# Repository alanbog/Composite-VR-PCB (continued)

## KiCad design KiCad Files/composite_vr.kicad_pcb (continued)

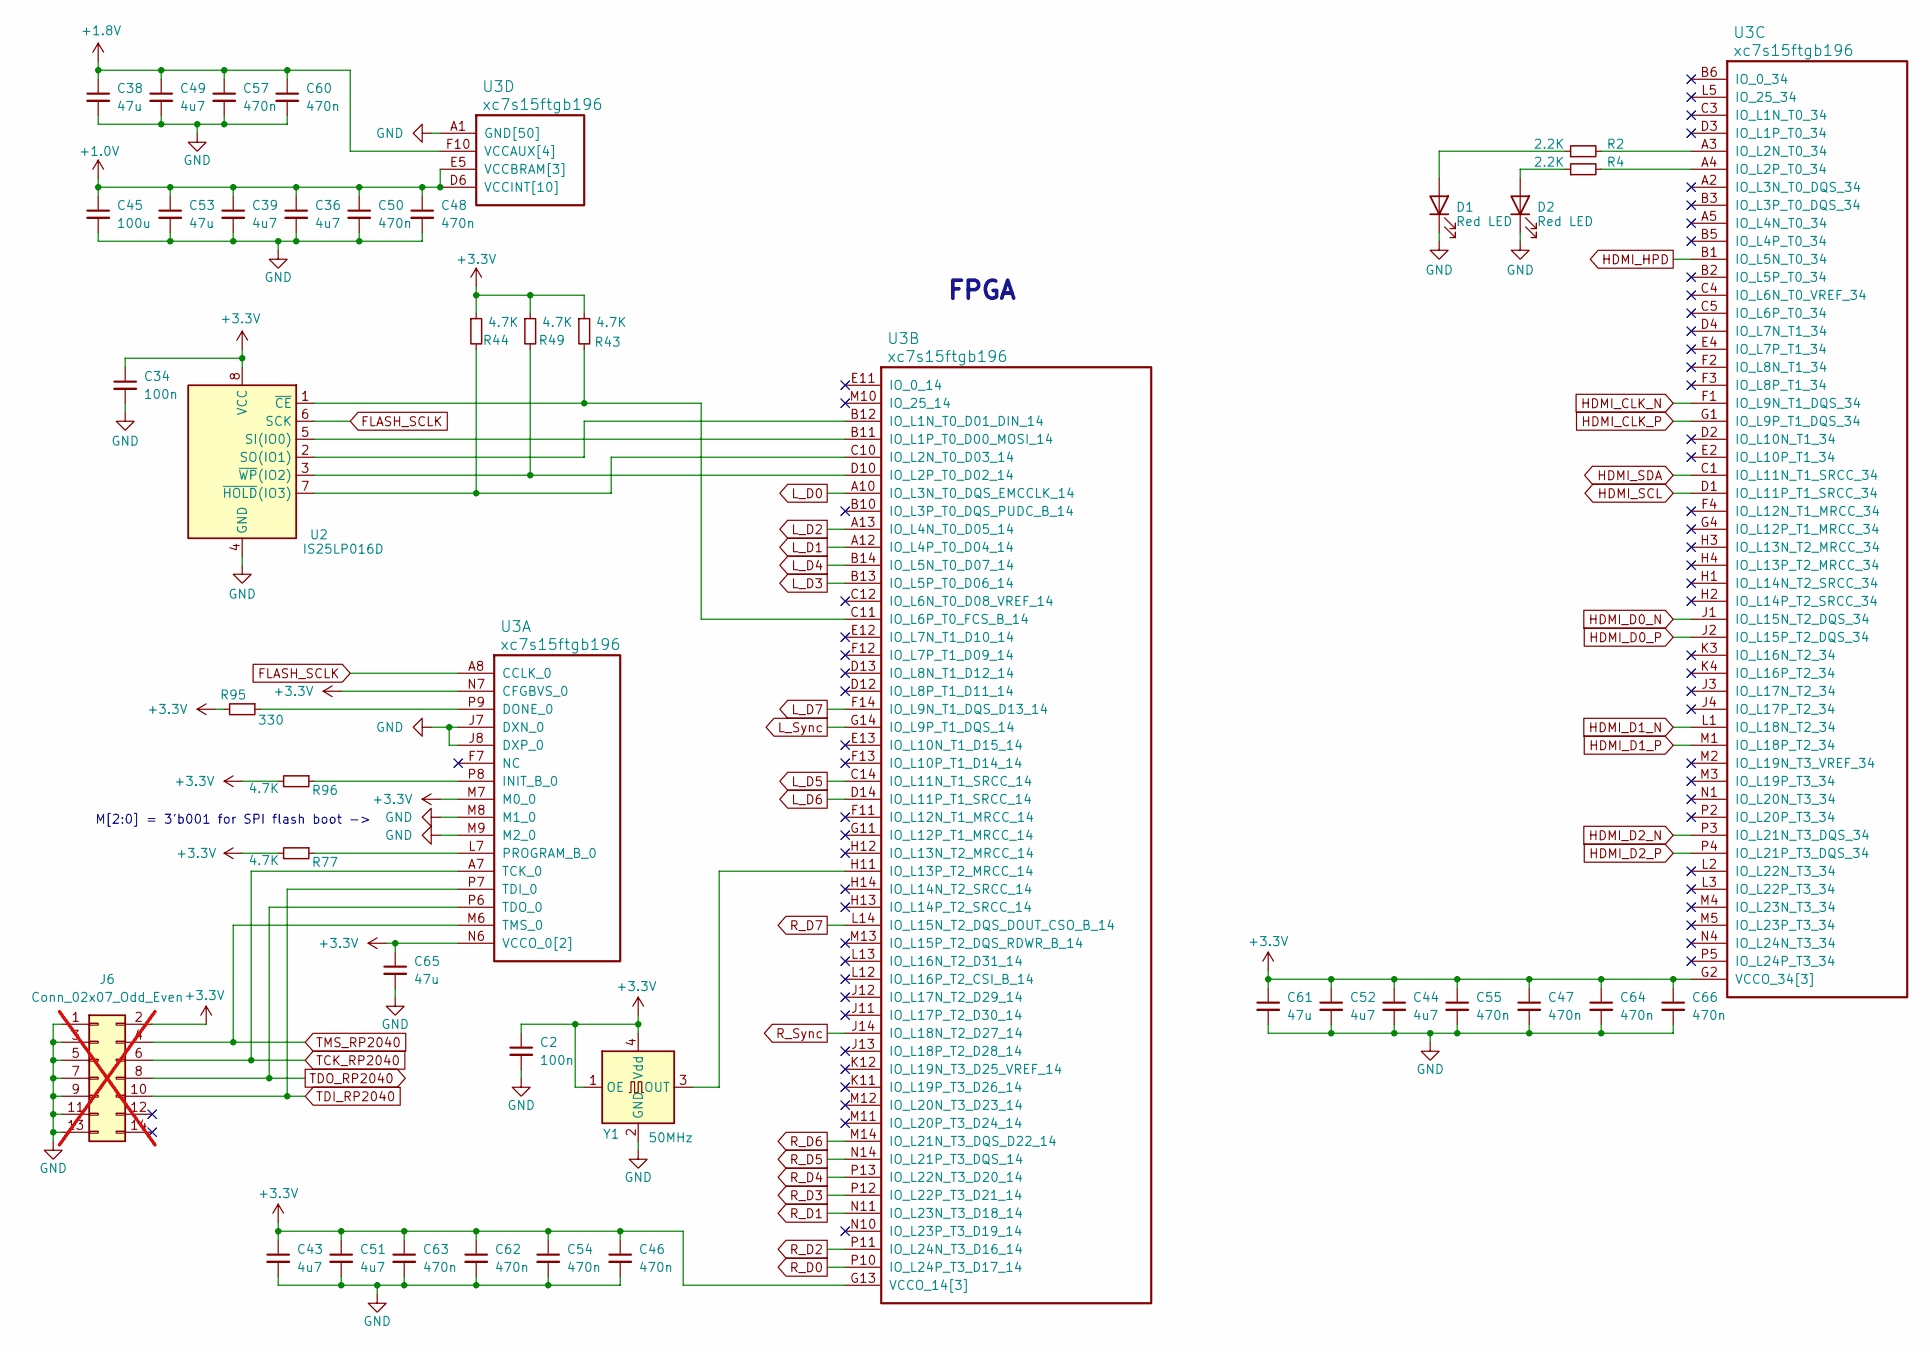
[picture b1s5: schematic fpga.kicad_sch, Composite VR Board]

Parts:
C2, C34: 100n; C_0402; Rating 16V; Tolerance 10%; Mfg PN CL05B104KO5NNNC; JLCPCB C1525
C36, C39, C43, C44, C49, C51, C52: 4u7; C_0402; Rating 10V; Tolerance 20%; Mfg PN CL05A475MP5NRNC; JLCPCB C23733
C38, C53, C61, C65: 47u; C_0805; Rating 6.3V; Tolerance 20%; Mfg PN CL21A476MQYNNNE; JLCPCB C16780
C45: 100u; C_1206; Rating 6.3V; Tolerance 20%; Mfg PN CL31A107MQHNNNE; JLCPCB C15008
C46, C47, C48, C50, C54, C55, C57, C60, C62, C63, C64, C66: 470n; C_0402; Rating 10V; Tolerance 10%; Mfg PN CL05A474KP5NNNC; JLCPCB C47339
D1, D2: Red LED; LED_0603_1608Metric; Mfg PN KT-0603R; JLCPCB C2286
J6: Conn_02x07_Odd_Even; PinHeader_2x07_P2.00mm_Vertical_SMD; not fitted
R2, R4: 2.2K; R_0402; Rating 62.5mW; Tolerance 1%; Mfg PN 0402WGF2201TCE; JLCPCB C25879
R43, R44, R49, R77, R96: 4.7K; R_0402; Rating 62.5mW; Tolerance 1%; Mfg PN 0402WGF4701TCE; JLCPCB C25900
R95: 330; R_0402; Rating 62.5mW; Tolerance 1%; Mfg PN 0402WGF3300TCE; JLCPCB C25104
U2: IS25LP016D; SO-8_3.9x4.9mm_P1.27mm; Mfg PN IS25LP016D-JNLE-TR; JLCPCB C2653501
U3: xc7s15ftgb196; Xilinx_FTGB196; Mfg PN XC7S15-2FTGB196I; JLCPCB C1521865
Y1: 50MHz; Oscillator_SMD_SiT_PQFN-4Pin_3.2x2.5mm; Mfg PN SiT8008BI-22-33E-50.000000; JLCPCB C26267

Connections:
+1.0V: C36.1, C39.1, C45.1, C48.1, C50.1, C53.1, U3.D6 (VCCINT[10]), U3.D8 (VCCINT[10]), U3.E5 (VCCBRAM[3]), U3.E7 (VCCINT[10]), U3.E9 (VCCINT[10]), U3.F6 (VCCINT[10]), U3.G5 (VCCBRAM[3]), U3.G9 (VCCINT[10]), U3.H6 (VCCINT[10]), U3.J5 (VCCBRAM[3]), U3.J9 (VCCINT[10]), U3.K6 (VCCINT[10]), U3.K8 (VCCINT[10]); also elsewhere on the board
+1.8V: C38.1, C49.1, C57.1, C60.1, U3.F10 (VCCAUX[4]), U3.H10 (VCCAUX[4]), U3.K10 (VCCAUX[4]), U3.L9 (VCCAUX[4]); also elsewhere on the board
+3.3V: C2.1, C34.1, C43.1, C44.1, C46.1, C47.1, C51.1, C52.1, C54.1, C55.1, C61.1, C62.1, C63.1, C64.1, C65.1, C66.1, J6.2, R43.1, R44.1, R49.1, R77.2, R95.2, R96.2, U2.8 (VCC), U3.G2 (VCCO_34[3]), U3.G13 (VCCO_14[3]), U3.K2 (VCCO_34[3]), U3.K13 (VCCO_14[3]), U3.M7 (M0_0), U3.N2 (VCCO_34[3]), U3.N6 (VCCO_0[2]), U3.N7 (CFGBVS_0), U3.N8 (VCCO_0[2]), U3.N13 (VCCO_14[3]), Y1.1 (OE), Y1.4 (Vdd); also elsewhere on the board
FLASH_SCLK: U2.6 (SCK), U3.A8 (CCLK_0)
GND: C2.2, C34.2, C36.2, C38.2, C39.2, C43.2, C44.2, C45.2, C46.2, C47.2, C48.2, C49.2, C50.2, C51.2, C52.2, C53.2, C54.2, C55.2, C57.2, C60.2, C61.2, C62.2, C63.2, C64.2, C65.2, C66.2, D1.1 (K), D2.1 (K), J6.1, J6.3, J6.5, J6.7, J6.9, J6.11, J6.13, U2.4 (GND), U3.A1 (GND[50]), U3.A6 (GND[50]), U3.A9 (GND[50]), U3.A11 (GND[50]), U3.A14 (GND[50]), U3.B4 (GND[50]), U3.B7 (GND[50]), U3.B9 (GND[50]), U3.C2 (GND[50]), U3.C6 (GND[50]), U3.C7 (GND[50]), U3.C8 (GND[50]), U3.C9 (GND[50]), U3.C13 (GND[50]), U3.D5 (GND[50]), U3.D7 (GND[50]), U3.D9 (GND[50]), U3.D11 (GND[50]), U3.E1 (GND[50]), U3.E3 (GND[50]), U3.E6 (GND[50]), U3.E8 (GND[50]), U3.E10 (GND[50]), U3.E14 (GND[50]), U3.F5 (GND[50]), U3.F9 (GND[50]), U3.G3 (GND[50]), U3.G6 (GND[50]), U3.G10 (GND[50]), U3.G12 (GND[50]), U3.H5 (GND[50]), U3.H9 (GND[50]), U3.J6 (GND[50]), U3.J7 (DXN_0), U3.J8 (DXP_0), U3.J10 (GND[50]), U3.K1 (GND[50]), U3.K5 (GND[50]), U3.K7 (GND[50]), U3.K9 (GND[50]), U3.K14 (GND[50]), U3.L4 (GND[50]), U3.L6 (GND[50]), U3.L8 (GND[50]), U3.L10 (GND[50]), U3.L11 (GND[50]), U3.M8 (M1_0), U3.M9 (M2_0), U3.N3 (GND[50]), U3.N5 (GND[50]), U3.N9 (GND[50]), U3.N12 (GND[50]), U3.P1 (GND[50]), U3.P14 (GND[50]), Y1.2 (GND); also elsewhere on the board
HDMI_CLK_N: U3.F1 (IO_L9N_T1_DQS_34); also elsewhere on the board
HDMI_CLK_P: U3.G1 (IO_L9P_T1_DQS_34); also elsewhere on the board
HDMI_D0_N: U3.J1 (IO_L15N_T2_DQS_34); also elsewhere on the board
HDMI_D0_P: U3.J2 (IO_L15P_T2_DQS_34); also elsewhere on the board
HDMI_D1_N: U3.L1 (IO_L18N_T2_34); also elsewhere on the board
HDMI_D1_P: U3.M1 (IO_L18P_T2_34); also elsewhere on the board
HDMI_D2_N: U3.P3 (IO_L21N_T3_DQS_34); also elsewhere on the board
HDMI_D2_P: U3.P4 (IO_L21P_T3_DQS_34); also elsewhere on the board
HDMI_HPD: U3.B1 (IO_L5N_T0_34); also elsewhere on the board
HDMI_SCL: U3.D1 (IO_L11P_T1_SRCC_34); also elsewhere on the board
HDMI_SDA: U3.C1 (IO_L11N_T1_SRCC_34); also elsewhere on the board
L_D0: U3.A10 (IO_L3N_T0_DQS_EMCCLK_14); also elsewhere on the board
L_D1: U3.A12 (IO_L4P_T0_D04_14); also elsewhere on the board
L_D2: U3.A13 (IO_L4N_T0_D05_14); also elsewhere on the board
L_D3: U3.B13 (IO_L5P_T0_D06_14); also elsewhere on the board
L_D4: U3.B14 (IO_L5N_T0_D07_14); also elsewhere on the board
L_D5: U3.C14 (IO_L11N_T1_SRCC_14); also elsewhere on the board
L_D6: U3.D14 (IO_L11P_T1_SRCC_14); also elsewhere on the board
L_D7: U3.F14 (IO_L9N_T1_DQS_D13_14); also elsewhere on the board
L_Sync: U3.G14 (IO_L9P_T1_DQS_14); also elsewhere on the board
unnamed: D1.2 (A), R2.1
unnamed: D2.2 (A), R4.1
unnamed: U2.5 (SI(IO0)), U3.B11 (IO_L1P_T0_D00_MOSI_14)
unnamed: U2.2 (SO(IO1)), U3.B12 (IO_L1N_T0_D01_DIN_14)
unnamed: R43.2, U2.1 (~CE), U3.C11 (IO_L6P_T0_FCS_B_14)
unnamed: R44.2, U2.7 (~HOLD(IO3)), U3.C10 (IO_L2N_T0_D03_14)
unnamed: R49.2, U2.3 (~WP(IO2)), U3.D10 (IO_L2P_T0_D02_14)
unnamed: R95.1, U3.P9 (DONE_0)
unnamed: R96.1, U3.P8 (INIT_B_0)
unnamed: R77.1, U3.L7 (PROGRAM_B_0)
unnamed: U3.H11 (IO_L13P_T2_MRCC_14), Y1.3 (OUT)
unnamed: R2.2, U3.A3 (IO_L2N_T0_34)
unnamed: R4.2, U3.A4 (IO_L2P_T0_34)
R_D0: U3.P10 (IO_L24P_T3_D17_14); also elsewhere on the board
R_D1: U3.N11 (IO_L23N_T3_D18_14); also elsewhere on the board
R_D2: U3.P11 (IO_L24N_T3_D16_14); also elsewhere on the board
R_D3: U3.P12 (IO_L22P_T3_D21_14); also elsewhere on the board
R_D4: U3.P13 (IO_L22N_T3_D20_14); also elsewhere on the board
R_D5: U3.N14 (IO_L21P_T3_DQS_14); also elsewhere on the board
R_D6: U3.M14 (IO_L21N_T3_DQS_D22_14); also elsewhere on the board
R_D7: U3.L14 (IO_L15N_T2_DQS_DOUT_CSO_B_14); also elsewhere on the board
R_Sync: U3.J14 (IO_L18N_T2_D27_14); also elsewhere on the board
TCK_RP2040: J6.6, U3.A7 (TCK_0); also elsewhere on the board
TDI_RP2040: J6.10, U3.P7 (TDI_0); also elsewhere on the board
TDO_RP2040: J6.8, U3.P6 (TDO_0); also elsewhere on the board
TMS_RP2040: J6.4, U3.M6 (TMS_0); also elsewhere on the board

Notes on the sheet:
FPGA
M[2:0] = 3'b001 for SPI flash boot ->

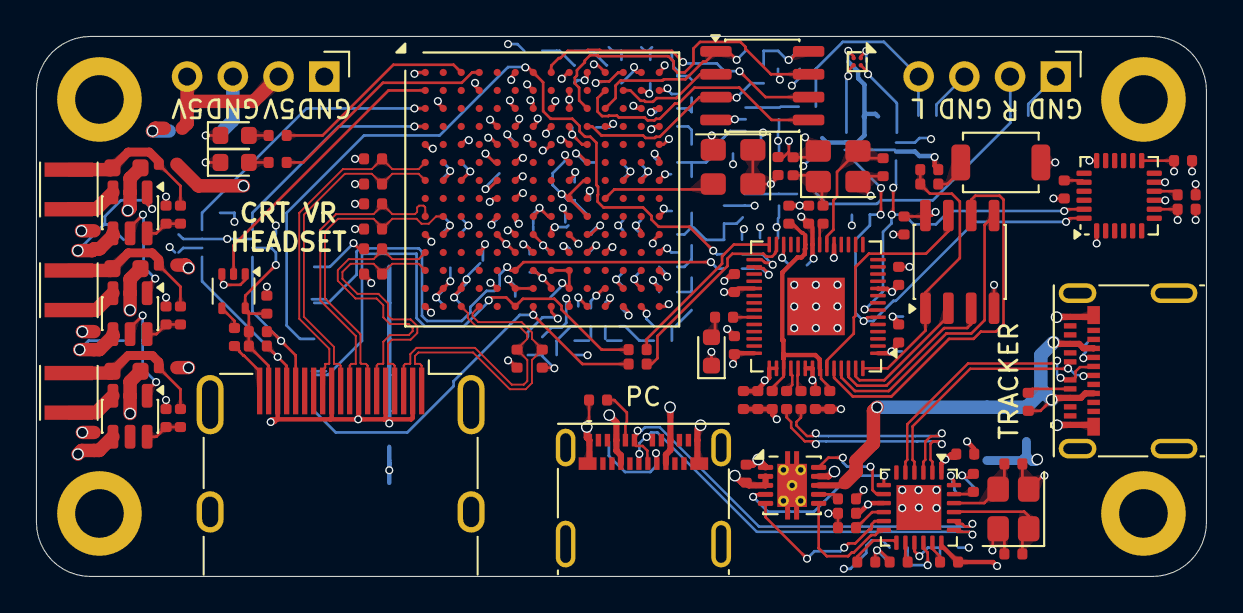
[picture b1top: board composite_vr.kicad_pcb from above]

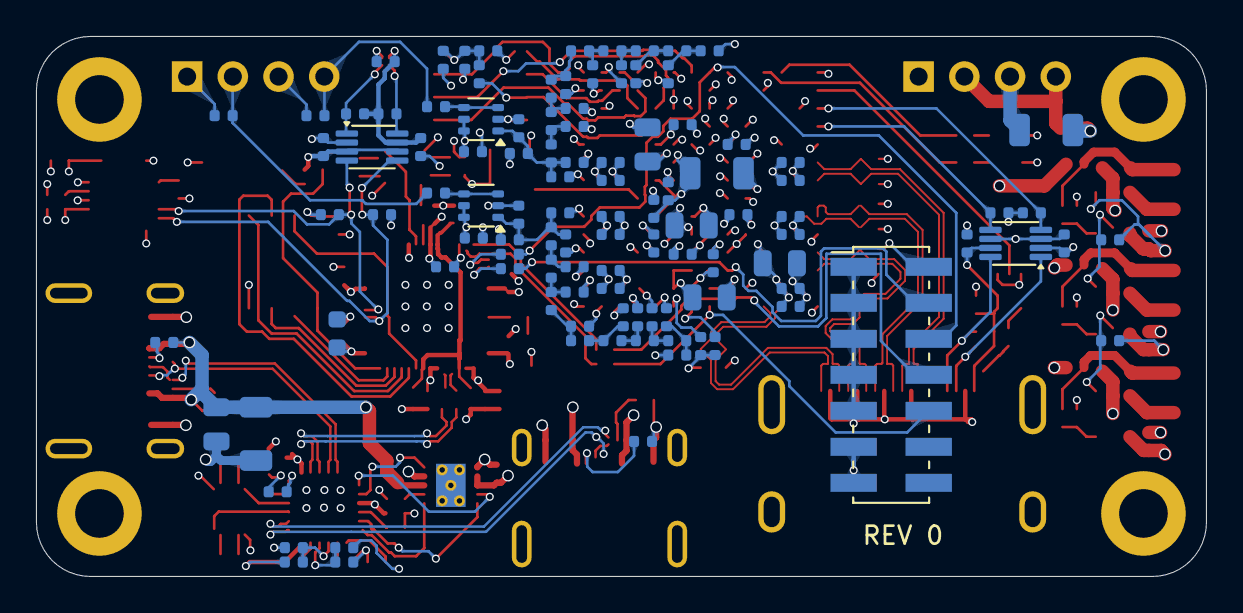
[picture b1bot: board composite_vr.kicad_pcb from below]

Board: 4 copper layers, 65.0 x 30.0 mm, 208 parts (107 on the bottom side), 142 nets.

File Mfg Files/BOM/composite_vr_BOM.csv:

"Reference","Qty","Value","Tolerance","Rating","DNP","Footprint","Mfg","Mfg PN","JLCPCB"
"C1,C2,C7,C8,C9,C10,C11,C14,C15,C16,C17,C19,C21,C24,C25,C27,C29,C30,C34,C42,C56,C58,C59,C70","24","100n","10%","16V","","PCM_JLCPCB:C_0402","Samsung Electro-Mechanics","CL05B104KO5NNNC","C1525"
"C3,C5,C28,C33","4","15p","5%","50V","","PCM_JLCPCB:C_0402","FH (Guangdong Fenghua Advanced Tech)"," 0402CG150J500NT","C1548"
"C4,C13,C20,C67","4","10u","10%","10V","","PCM_JLCPCB:C_0603","Samsung Electro-Mechanics","CL10A106KP8NNNC","C19702"
"C6","1","2.2n","10%","50V","","PCM_JLCPCB:C_0402","FH (Guangdong Fenghua Advanced Tech)","0402B222K500NT","C1531"
"C12,C18,C26,C36,C39,C43,C44,C49,C51,C52","10","4u7","20%","10V","","PCM_JLCPCB:C_0402","Samsung Electro-Mechanics","CL05A475MP5NRNC","C23733"
"C22,C23,C31,C32","4","1u","10%","25V","","PCM_JLCPCB:C_0402","Samsung Electro-Mechanics","CL05A105KA5NQNC","C52923"
"C35,C40,C41","3","100n","10%","16V","DNP","PCM_JLCPCB:C_0402","Samsung Electro-Mechanics","CL05B104KO5NNNC","C1525"
"C37,C45,C69","3","100u","20%","6.3V","","PCM_JLCPCB:C_1206","Samsung Electro-Mechanics","CL31A107MQHNNNE","C15008"
"C38,C53,C61,C65,C68","5","47u","20%","6.3V","","PCM_JLCPCB:C_0805","Samsung Electro-Mechanics","CL21A476MQYNNNE","C16780"
"C46,C47,C48,C50,C54,C55,C57,C60,C62,C63,C64,C66","12","470n","10%","10V","","PCM_JLCPCB:C_0402","Samsung Electro-Mechanics","CL05A474KP5NNNC","C47339"
"D1,D2,D3","3","Red LED","","","","LED_SMD:LED_0603_1608Metric","Hubei KENTO Elec","KT-0603R","C2286"
"J1,J2","2","Conn_01x04","","","DNP","Connector_PinHeader_2.54mm:PinHeader_1x04_P2.54mm_Vertical","","","-"
"J3,J5","2","USB_C_Receptacle","","","","Connector_USB:USB_C_Receptacle_Molex_105450-0101","MOLEX","1054500101","C134092"
"J4","1","HDMI_A","","","","Connector_Video:HDMI_A_Molex_208658-1001_Horizontal","XUNPU","HDMI-001S","C720616"
"J6","1","Conn_02x07_Odd_Even","","","DNP","Connector_PinHeader_2.00mm:PinHeader_2x07_P2.00mm_Vertical_SMD","","",""
"L1,L2,L3","3","2u2","","","","Inductor_SMD:L_Taiyo-Yuden_MD-3030","Murata Electronics","LQH3NPN2R2MJRL","C341775"
"R1,R5,R15,R23,R26,R27,R64,R66,R76,R80","10","0","1%","62.5mW","","PCM_JLCPCB:R_0402","UNI-ROYAL(Uniroyal Elec)","0402WGF0000TCE","C17168"
"R2,R4,R19,R20,R22","5","2.2K","1%","62.5mW","","PCM_JLCPCB:R_0402","UNI-ROYAL(Uniroyal Elec)","0402WGF2201TCE","C25879"
"R3,R7,R9,R13,R14,R16,R24,R25","8","49.9","1%","62.5mW","","PCM_JLCPCB:R_0402","UNI-ROYAL(Uniroyal Elec)","0402WGF499JTCE","C25120"
"R6,R78","2","10K","1%","62.5mW","","PCM_JLCPCB:R_0402","UNI-ROYAL(Uniroyal Elec)","0402WGF1002TCE","C25744"
"R8,R12,R21","3","1K","1%","62.5mW","","PCM_JLCPCB:R_0402","UNI-ROYAL(Uniroyal Elec)","0402WGF1001TCE","C11702"
"R10,R34","2","33K","1%","62.5mW","","PCM_JLCPCB:R_0402","UNI-ROYAL(Uniroyal Elec)","0402WGF3302TCE","C25779"
"R11,R31,R32,R94","4","22K","1%","62.5mW","","PCM_JLCPCB:R_0402","UNI-ROYAL(Uniroyal Elec)","0402WGF2202TCE","C25768"
"R17,R33,R35,R36,R37,R100,R101,R102","8","100K","1%","62.5mW","","PCM_JLCPCB:R_0402","UNI-ROYAL(Uniroyal Elec)","0402WGF1003TCE","C25741"
"R18,R74,R93","3","200K","1%","62.5mW","","PCM_JLCPCB:R_0402","UNI-ROYAL(Uniroyal Elec)","0402WGF2003TCE","C25764"
"R28,R98","2","5.1K","1%","62.5mW","","PCM_JLCPCB:R_0402","UNI-ROYAL(Uniroyal Elec)","0402WGF5101TCE","C25905"
"R29,R30","2","22","1%","62.5mW","","PCM_JLCPCB:R_0402","UNI-ROYAL(Uniroyal Elec)","0402WGF220JTCE","C25092"
"R38,R39,R40,R41,R51,R58,R62,R72,R81,R83,R89,R90,R91,R92","14","7.5K","0.1%","62.5mW","","PCM_JLCPCB:R_0402","UNI-ROYAL(Uniroyal Elec)","TC0225B7501TCC","C28566374"
"R42,R45,R46,R47,R48,R50,R53,R59,R63,R75,R79,R82,R84,R85,R86,R87,R88,R97","18","15K","0.1%","62.5mW","","PCM_JLCPCB:R_0402","FH (Guangdong Fenghua Advanced Tech)","TC02G1502BT","C20627044"
"R43,R44,R49,R67,R68,R69,R70,R77,R96","9","4.7K","1%","62.5mW","","PCM_JLCPCB:R_0402","UNI-ROYAL(Uniroyal Elec)","0402WGF4701TCE","C25900"
"R52,R65","2","75","1%","62.5mW","","PCM_JLCPCB:R_0402","UNI-ROYAL(Uniroyal Elec)","0402WGF750JTCE","C25133"
"R54,R55","2","4.7K","1%","62.5mW","DNP","PCM_JLCPCB:R_0402","UNI-ROYAL(Uniroyal Elec)","0402WGF4701TCE","C25900"
"R56,R57","2","75","1%","62.5mW","DNP","PCM_JLCPCB:R_0402","UNI-ROYAL(Uniroyal Elec)","0402WGF750JTCE","C25133"
"R60,R71","2","8.2K","1%","62.5mW","","PCM_JLCPCB:R_0402","UNI-ROYAL(Uniroyal Elec)","0402WGF8201TCE","C25924"
"R61,R73","2","18K","1%","62.5mW","","PCM_JLCPCB:R_0402","UNI-ROYAL(Uniroyal Elec)","0402WGF1802TCE","C25762"
"R95","1","330","1%","62.5mW","","PCM_JLCPCB:R_0402","UNI-ROYAL(Uniroyal Elec)","0402WGF3300TCE","C25104"
"R99","1","12K","1%","62.5mW","","PCM_JLCPCB:R_0402","UNI-ROYAL(Uniroyal Elec)","0402WGF1202TCE","C25752"
"SW1","1","SW_Push","","","","Button_Switch_SMD:SW_SPST_TS-1088-xR025","XUNPU","TS-1088-AR02016","C720477"
"U1","1","AK09918C","","","DNP","Package_BGA:WLP-4_0.83x0.83mm_P0.4mm","Asahi Kasei Microdevices","AK09918C","C2655004"
"U2,U6","2","IS25LP016D","","","","Package_SO:SO-8_3.9x4.9mm_P1.27mm","ISSI(Integrated Silicon Solution)","IS25LP016D-JNLE-TR","C2653501"
"U3","1","xc7s15ftgb196","","","","Package_BGA:Xilinx_FTGB196","AMD/XILINX"," XC7S15-2FTGB196I","C1521865"
"U4","1","MPU-6050","","","","Sensor_Motion:InvenSense_QFN-24_4x4mm_P0.5mm"," TDK InvenSense","MPU-6050","C24112"
"U5,U9,U10","3","TLV62568PDDCR","","","","Library:SOT-23-6-small_courtyard","Texas Instruments","TLV62568PDDCR","C398369"
"U7","1","NC7SZ125P5X","","","","Package_TO_SOT_SMD:SOT-353_SC-70-5","onsemi","NC7SZ125P5X","C112084"
"U8","1","RP2040","","","","Package_DFN_QFN:QFN-56-1EP_7x7mm_P0.4mm_EP3.2x3.2mm","Raspberry Pi","RP2040","C2040"
"U11","1","TPS2561","","","","Package_SON:VSON-10-1EP_3x3mm_P0.5mm_EP1.65x2.4mm_ThermalVias","Texas Instruments","TPS2561DRCR","C140303"
"U12","1","USB2422","","","","Package_DFN_QFN:QFN-24-1EP_4x4mm_P0.5mm_EP2.5x2.5mm","Microchip Tech","USB2422T/MJ","C622611"
"U13,U15","2","OPA358","","","","Package_TO_SOT_SMD:SOT-363_SC-70-6","Texas Instruments","OPA358AIDCKT","C2057755"
"U14","1","TXS0102DCU","","","DNP","Package_SO:VSSOP-8_2.3x2mm_P0.5mm","Texas Instruments","TXS0102DCUR","C53434"
"U16","1","TXS0102DCU","","","","Package_SO:VSSOP-8_2.3x2mm_P0.5mm","Texas Instruments","TXS0102DCUR","C53434"
"Y1","1","50MHz","","","","Oscillator:Oscillator_SMD_SiT_PQFN-4Pin_3.2x2.5mm","SiTime","SiT8008BI-22-33E-50.000000","C26267"
"Y2","1","12MHz","","","","Crystal:Crystal_SMD_3225-4Pin_3.2x2.5mm","SJK(SHENZHEN CRYSTAL TECH)","7U12000E09UCG","C524716"
"Y3","1","24MHz","","","","Crystal:Crystal_SMD_3225-4Pin_3.2x2.5mm","SJK(SHENZHEN CRYSTAL TECH)","7U24000E09UCG","C251611"

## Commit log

2026-06-29 Enhance README with detailed project description
    Expanded the README to include detailed information about the controller board's functionality, components, and usage with Vive Tracker.
2026-06-29 Add image for composite VR setup in README
    Added an image to the README for visual reference.
2026-06-29 Update README with Relativty reference
    Added reference to Relativty for IMU tracking data transmission.
